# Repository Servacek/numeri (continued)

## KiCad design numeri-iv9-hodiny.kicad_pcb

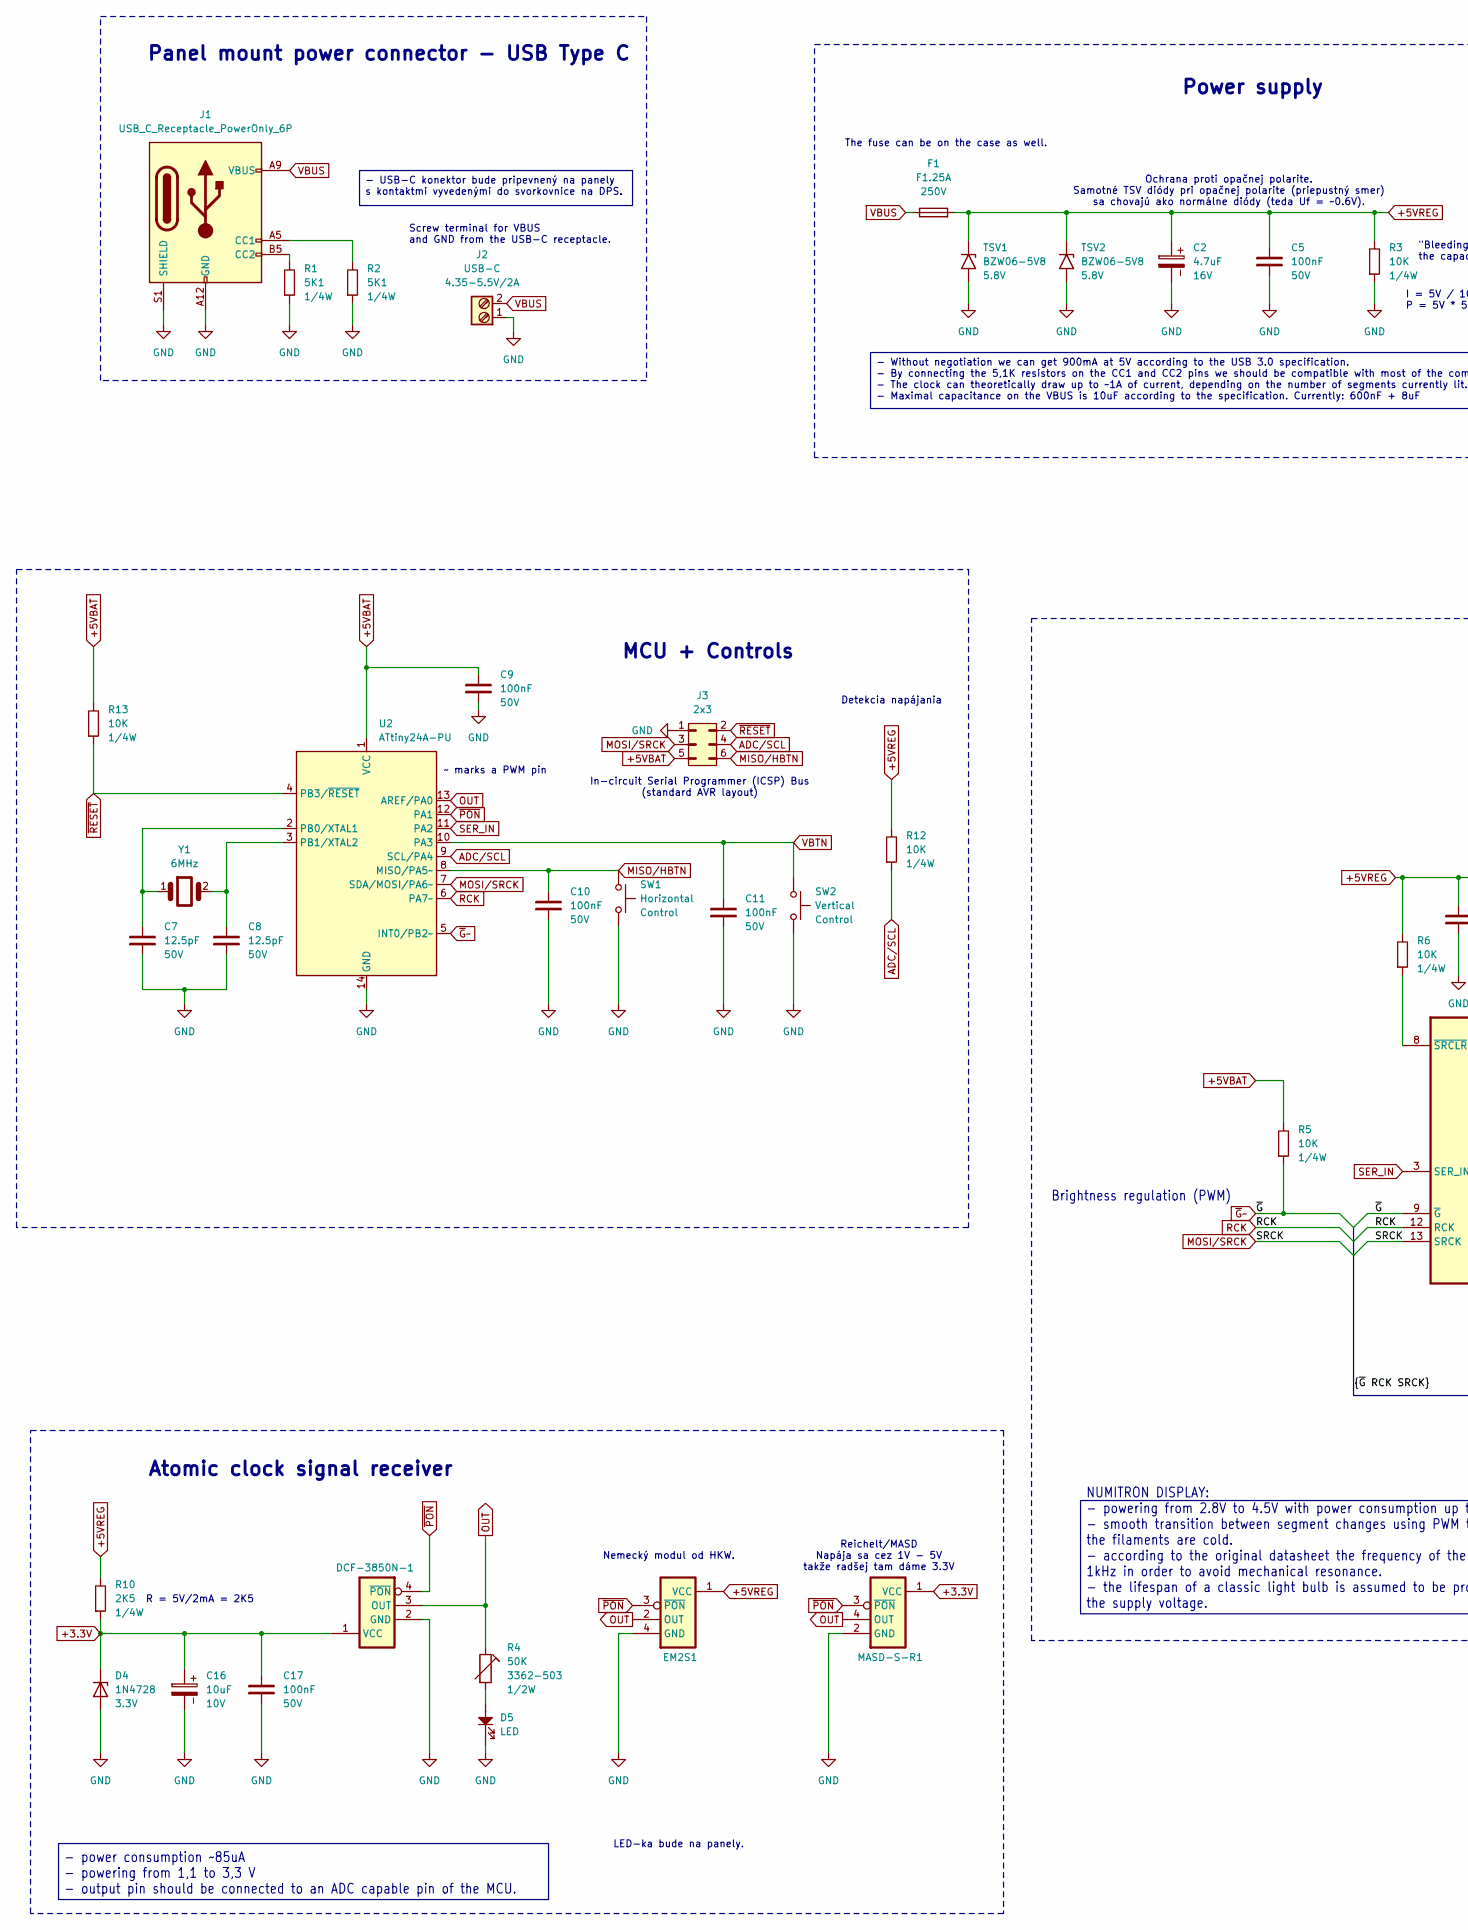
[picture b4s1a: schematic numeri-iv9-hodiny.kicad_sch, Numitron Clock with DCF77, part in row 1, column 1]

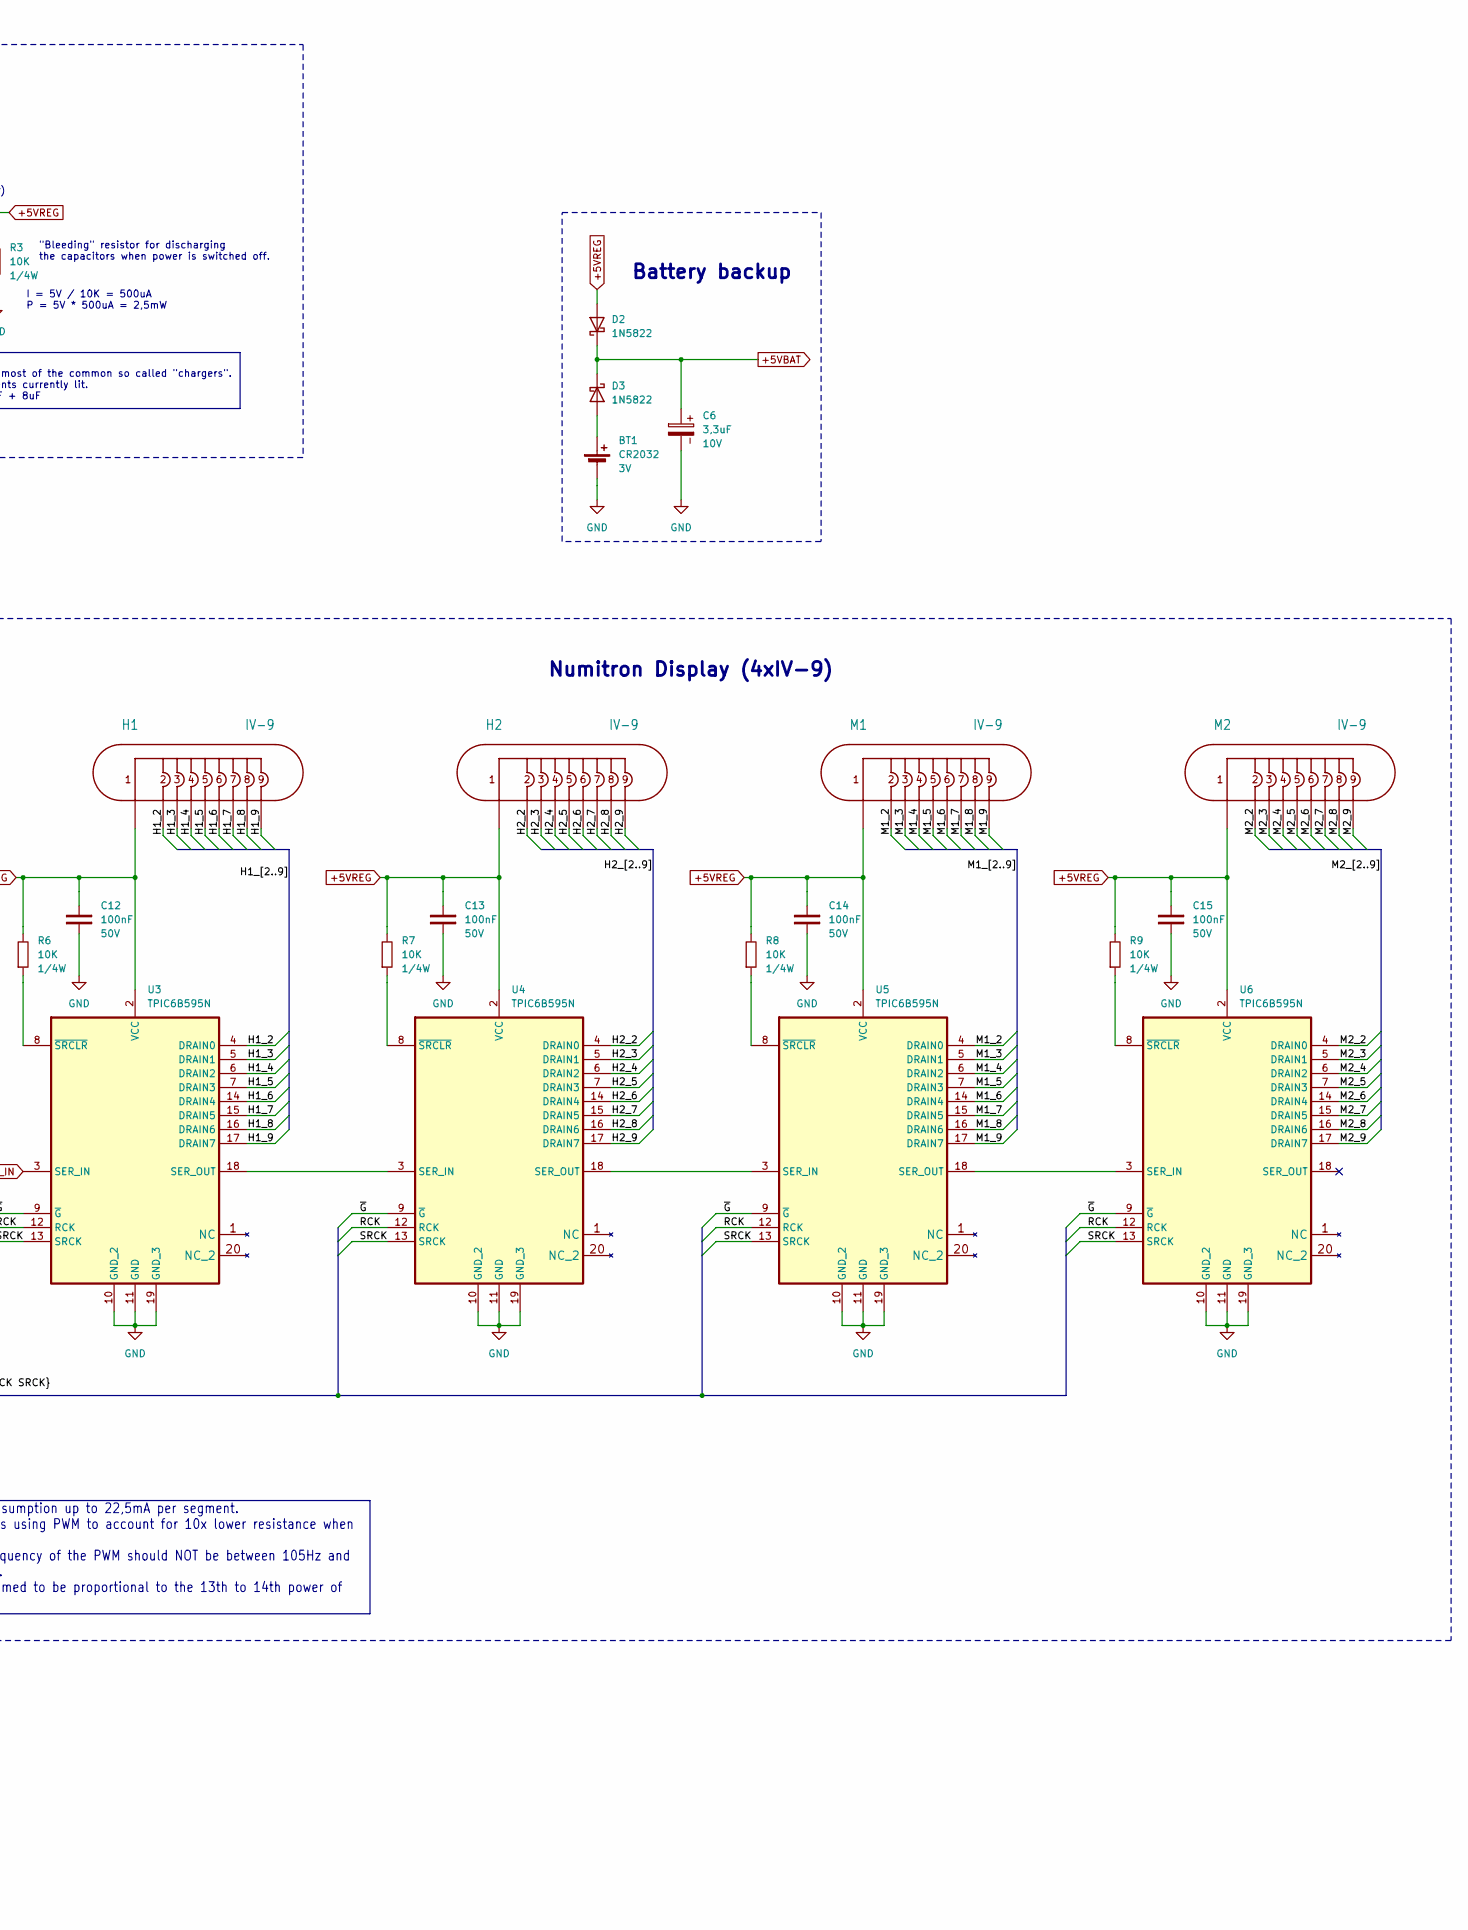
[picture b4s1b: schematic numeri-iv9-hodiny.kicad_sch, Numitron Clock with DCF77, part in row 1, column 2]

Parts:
BT1: CR2032; BatteryHolder_Keystone_CR2032_Vertical; Voltage 3V
C2: 4.7uF; CP_Radial_D5.0mm_P2.00mm; Voltage 16V
C5, C9, C10, C11, C12, C13, C14, C15, C17: 100nF; C_Disc_D3.0mm_W2.0mm_P2.50mm
C6: 3,3uF; CP_Radial_D5.0mm_P2.00mm; Voltage 10V
C7, C8: 12.5pF; C_Disc_D3.0mm_W2.0mm_P2.50mm
C16: 10uF; CP_Radial_D5.0mm_P2.00mm
D2, D3: 1N5822; D_DO-41_SOD81_P10.16mm_Horizontal
D4: 1N4728; D_DO-41_SOD81_P10.16mm_Horizontal
D5: LED; TerminalBlock_Phoenix_MPT-0,5-2-2.54_1x02_P2.54mm_Horizontal
DCF-3850N-1: DCF77; PinSocket_1x04_P2.54mm_Vertical
EM2S1: DCF77; PinSocket_1x04_P2.54mm_Vertical
F1: F1.25A; Fuseholder_Cylinder-5x20mm_Schurter_0031_8201_Horizontal_Op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; Voltage 250V
H1, H2: IV-9; IV-9_External_Socket_Asymetric
J1: USB_C_Receptacle_PowerOnly_6P
J2: USB-C; TerminalBlock_Phoenix_PT-1,5-2-5.0-H_1x02_P5.00mm_Horizontal
J3: 2x3; PinHeader_2x03_P2.54mm_Vertical
M1, M2: IV-9; IV-9_External_Socket_Asymetric
MASD-S-R1: DCF77; PinSocket_1x04_P2.54mm_Vertical
R1, R2: 5K1; R_Axial_DIN0207_L6.3mm_D2.5mm_P10.16mm_Horizontal
R3: 10K; R_Axial_DIN0207_L6.3mm_D2.5mm_P2.54mm_Vertical
R4: 50K; potentiometer_3362P
R5, R12, R13: 10K; R_Axial_DIN0207_L6.3mm_D2.5mm_P5.08mm_Vertical
R6, R7, R8, R9: 10K; R_Axial_DIN0207_L6.3mm_D2.5mm_P10.16mm_Horizontal
R10: 2K5; R_Axial_DIN0207_L6.3mm_D2.5mm_P10.16mm_Horizontal
SW1: Horizontal; TerminalBlock_Phoenix_MPT-0,5-2-2.54_1x02_P2.54mm_Horizontal
SW2: Vertical; TerminalBlock_Phoenix_MPT-0,5-2-2.54_1x02_P2.54mm_Horizontal
TSV1, TSV2: BZW06-5V8; D_DO-201AE_P15.24mm_Horizontal; Voltage 5.8V
U2: ATtiny24A-PU; DIP-14_W7.62mm_Socket
U3, U4, U5, U6: TPIC6B595N; DIP-20_W7.62mm_Socket
Y1: 6MHz; Crystal_HC49-4H_Vertical

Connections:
+3.3V: C16.1, C17.2, D4.1 (K), DCF-3850N-1.1 (VCC), MASD-S-R1.1 (VCC), R10.1
+5VBAT: C6.1, C9.2, D2.1 (K), D3.1 (K), J3.5, R5.2, R13.2, U2.1 (VCC)
+5VREG: C2.1, C5.2, C12.2, C13.2, C14.2, C15.2, D2.2 (A), EM2S1.1 (VCC), F1.2, H1.1, H2.1, M1.1, M2.1, R3.2, R6.2, R7.2, R8.2, R9.2, R10.2, R12.2, TSV1.1 (A1), TSV2.1 (A1), U3.2 (VCC), U4.2 (VCC), U5.2 (VCC), U6.2 (VCC)
/H1_2: H1.2, U3.4 (DRAIN0)
/H1_3: H1.3, U3.5 (DRAIN1)
/H1_4: H1.4, U3.6 (DRAIN2)
/H1_5: H1.5, U3.7 (DRAIN3)
/H1_6: H1.6, U3.14 (DRAIN4)
/H1_7: H1.7, U3.15 (DRAIN5)
/H1_8: H1.8, U3.16 (DRAIN6)
/H1_9: H1.9, U3.17 (DRAIN7)
/H2_2: H2.2, U4.4 (DRAIN0)
/H2_3: H2.3, U4.5 (DRAIN1)
/H2_4: H2.4, U4.6 (DRAIN2)
/H2_5: H2.5, U4.7 (DRAIN3)
/H2_6: H2.6, U4.14 (DRAIN4)
/H2_7: H2.7, U4.15 (DRAIN5)
/H2_8: H2.8, U4.16 (DRAIN6)
/H2_9: H2.9, U4.17 (DRAIN7)
/M1_2: M1.2, U5.4 (DRAIN0)
/M1_3: M1.3, U5.5 (DRAIN1)
/M1_4: M1.4, U5.6 (DRAIN2)
/M1_5: M1.5, U5.7 (DRAIN3)
/M1_6: M1.6, U5.14 (DRAIN4)
/M1_7: M1.7, U5.15 (DRAIN5)
/M1_8: M1.8, U5.16 (DRAIN6)
/M1_9: M1.9, U5.17 (DRAIN7)
/M2_2: M2.2, U6.4 (DRAIN0)
/M2_3: M2.3, U6.5 (DRAIN1)
/M2_4: M2.4, U6.6 (DRAIN2)
/M2_5: M2.5, U6.7 (DRAIN3)
/M2_6: M2.6, U6.14 (DRAIN4)
/M2_7: M2.7, U6.15 (DRAIN5)
/M2_8: M2.8, U6.16 (DRAIN6)
/M2_9: M2.9, U6.17 (DRAIN7)
ADC/SCL: J3.4, R12.1, U2.9 (SCL/PA4)
GND: BT1.2 (-), C2.2, C5.1, C6.2, C7.1, C8.1, C9.1, C10.1, C11.1, C12.1, C13.1, C14.1, C15.1, C16.2, C17.1, D4.2 (A), D5.1, DCF-3850N-1.2 (GND), EM2S1.4 (GND), J1.A12 (GND), J1.B12 (GND), J1.S1 (SHIELD), J2.1, J3.1, MASD-S-R1.2 (GND), R1.1, R2.1, R3.1, SW1.2, SW2.2, TSV1.2 (A2), TSV2.2 (A2), U2.14 (GND), U3.10 (GND_2), U3.11 (GND), U3.19 (GND_3), U4.10 (GND_2), U4.11 (GND), U4.19 (GND_3), U5.10 (GND_2), U5.11 (GND), U5.19 (GND_3), U6.10 (GND_2), U6.11 (GND), U6.19 (GND_3)
MISO/HBTN: C10.2, J3.6, SW1.1, U2.8 (MISO/PA5~)
MOSI/SRCK: J3.3, U2.7 (SDA/MOSI/PA6~), U3.13 (SRCK), U4.13 (SRCK), U5.13 (SRCK), U6.13 (SRCK)
unnamed: BT1.1 (+), D3.2 (A)
unnamed: D5.2, R4.2
unnamed: J1.A5 (CC1), R2.2
unnamed: J1.B5 (CC2), R1.2
unnamed: C7.2, U2.2 (PB0/XTAL1), Y1.1
unnamed: C8.2, U2.3 (PB1/XTAL2), Y1.2
unnamed: U3.18 (SER_OUT), U4.3 (SER_IN)
unnamed: R6.1, U3.8 (~SRCLR)
unnamed: U4.18 (SER_OUT), U5.3 (SER_IN)
unnamed: R7.1, U4.8 (~SRCLR)
unnamed: U5.18 (SER_OUT), U6.3 (SER_IN)
unnamed: R8.1, U5.8 (~SRCLR)
unnamed: R9.1, U6.8 (~SRCLR)
OUT: DCF-3850N-1.3 (OUT), EM2S1.2 (OUT), MASD-S-R1.4 (OUT), R4.1, U2.13 (AREF/PA0)
RCK: U2.6 (PA7~), U3.12 (RCK), U4.12 (RCK), U5.12 (RCK), U6.12 (RCK)
SER_IN: U2.11 (PA2), U3.3 (SER_IN)
VBTN: C11.2, SW2.1, U2.10 (PA3)
VBUS: F1.1, J1.A9 (VBUS), J1.B9 (VBUS), J2.2
~G~: R5.1, U2.5 (INT0/PB2~), U3.9 (~G), U4.9 (~G), U5.9 (~G), U6.9 (~G)
~PON: DCF-3850N-1.4 (~PON), EM2S1.3 (~PON), MASD-S-R1.3 (~PON), U2.12 (PA1)
~RESET: J3.2, R13.1, U2.4 (PB3/~RESET)

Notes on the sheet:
In-circuit Serial Programmer (ICSP) Bus (standard AVR layout)
The fuse can be on the case as well.
"Bleeding" resistor for discharging the capacitors when power is switched off.
Reichelt/MASD Napája sa cez 1V - 5V takže radšej tam dáme 3.3V
~ marks a PWM pin
Power supply
Battery backup
Screw terminal for VBUS and GND from the USB-C receptacle.
Detekcia napájania
I = 5V / 10K = 500uA P = 5V * 500uA = 2,5mW
MCU + Controls
Brightness regulation (PWM)
Ochrana proti opačnej polarite. Samotné TSV diódy pri opačnej polarite (priepustný smer) sa chovajú ako normálne diódy (teda Uf = ~0.6V).
Nemecký modul od HKW.
R = 5V/2mA = 2K5
LED-ka bude na panely.
Numitron Display (4xIV-9)
Atomic clock signal receiver
Panel mount power connector - USB Type C
NUMITRON DISPLAY: - powering from 2.8V to 4.5V with power consumption up to 22,5mA per segment. - smooth transition between segment changes using PWM to account for 10x lower resistance when the filaments are cold. - according to the original datasheet the frequency of the PWM should NOT be between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
- Without negotiation we can get 900mA at 5V according to the USB 3.0 specification. - By connecting the 5,1K resistors on the CC1 and CC2 pins we should be compatible with most of the common so called "chargers". - The clock can theoretically draw up to ~1A of current, depending on the number of s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
- power consumption ~85uA - powering from 1,1 to 3,3 V - output pin should be connected to an ADC capable pin of the MCU.
- USB-C konektor bude pripevnený na panely s kontaktmi vyvedenými do svorkovnice na DPS.

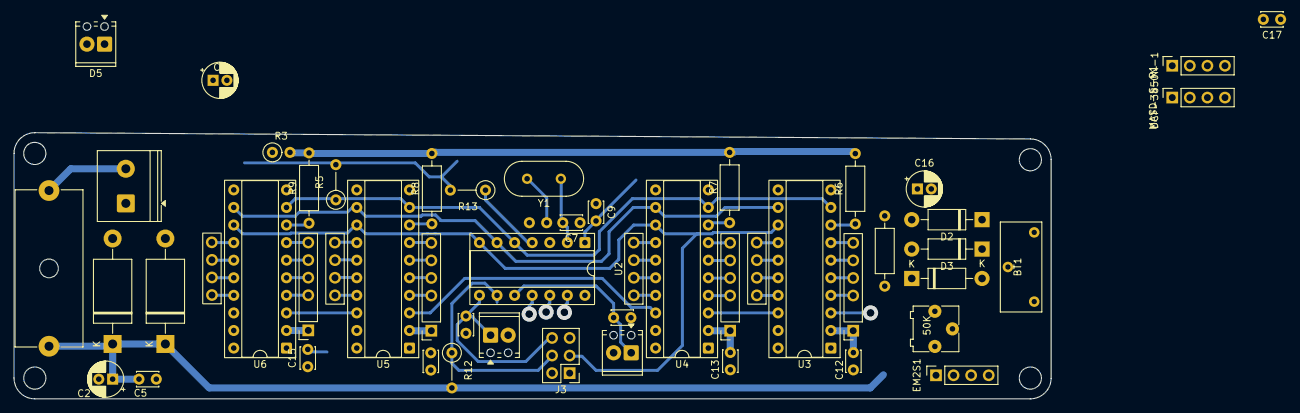
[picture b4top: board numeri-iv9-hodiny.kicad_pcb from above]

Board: 2 copper layers, 149.9 x 38.5 mm, 49 parts (1 on the bottom side), 58 nets.

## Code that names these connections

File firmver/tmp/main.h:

#ifndef NUMITRON_CLOCK_H
#define NUMITRON_CLOCK_H


#include <Arduino.h>
#include <EEPROM.h>


#define RESET_BUTTON        4
#define LEFT_BUTTON         3
#define RIGHT_BUTTON        2

#define LED_R               1 // PB1 (9 - 8)
#define LED_G               2 // PB2 (10 - 8)
#define LED_B               3 // PB3 (11 - 8)

#define DCF_OUT             A3 // PC3
#define DCF_PON             5  // PB5 (13 - 8)

#define LDR_PIN_PORTC       1 // A1

#define INA219_ADDR         0x40

// Tieto piny su uz pevne dane hardverom.
#define SERIN_PORTB         4 // PB4 (12 - 8)
#define SRCK_PORTB          0 // PB0 (8 - 8)
#define _G_PORTD            6 // PD6
#define RCK_PORTD           7 // PD7

#define SEGMENT_DP          7

#define DIGIT_COUNT         4

#define NUMBER_TRANS_DUR    3200 // ms
// Cim mensia hodnota, tym rychlejsie preklapanie.
#define CROSSFADING_WRAP    1
#define NUMBER_TRANS_PER    (NUMBER_TRANS_DUR / CROSSFADING_WRAP)

// Realne maximum je samozrejme 255 ale to by znamelo celych 5V pre numitrony
// co je nad maximalnu hodnotu stanovenu v dokumentacii.
// Takze mame hardverove maximum a softverove maximum.
#define MAX_BRIGHTNESS      127 //160
#define DEFAULT_BRIGHTNESS  MAX_BRIGHTNESS / 2
#define MINIMUM_BRIGHTNESS  10

#define DIGIT_MIN_UNITS     3
#define DIGIT_MIN_TENS      2
#define DIGIT_HOR_UNITS     1
#define DIGIT_HOR_TENS      0

#define DIGIT_MASK          0b01111111 // mask non-digit segments

#define EDIT_MODE_BLINK_F   200 // ms

#define LONG_PRESS_DELAY    2000 // ms

#define ON                  1
#define OFF                 0

#define PRESSED             0
#define RELEASED            1

#define NUM_SYMBOL_COUNT    10

#define MAX_MINUTES_COUNT   (24 * 60)

// Bit helpers
#define BIS(reg, bit)       (reg & (1 << bit))
#define SBI(reg, bit)       (reg |= (1 << bit))
#define CBI(reg, bit)       (reg &= ~(1 << bit))

#define PWM_REGISTER        OCR0A

// trvanie = 1 / 16 000 000 = 6,25 * 10^-8 s = 62,5 ns
#define NOP __asm__ __volatile__ ("nop\n\t")

// const byte CROSSFADING_FLIP_VALUES[] PROGMEM = {
//   20, 18, 16, 14, 13, 11, 10, 9, 8, 7, 6, 5, 4, 3, 2, 1
// };

// ---- EEPROM configuration addresses & enums ----
enum CONFIG {
  HOURS,
  MINUTES,
  BRIGHTNESS,
  GENERAL, // bit positions according to CONFIG_GENERAL
};

enum CONFIG_GENERAL {
  M12_24,        // 12/24h mode
  TRAILLING_ZERO, // show leading tens-hour zero
  NIGHT_MODE_ENABLED,
  NIGHT_MODE_TYPE,
};

// inline void SET(uint8_t pin, bool state) {
//     if (pin < 0) {
//         return;
//     }

//     if (pin <= 7) {
//         if (state) {
//             SBI(PORTD, pin);
//         } else {
//             CBI(PORTD, pin);
//         }
//     } else if (pin <= 13) {
//         if (state) {
//             SBI(PORTB, pin - 8);
//         } else {
//             CBI(PORTB, pin - 8);
//         }
//     } else if (pin <= A6) {
//         if (state) {
//             SBI(PORTC, pin - A0);
//         } else {
//             CBI(PORTC, pin - A0);
//         }
//     }
// }

// ---- Externs for globals defined in the sketch (.ino/.cpp) ----
extern byte LAZY_EE[];                    // lazy EEPROM cache
extern const byte NUM_SYMBOL_BYTES[];     // 7-seg bitmap -> symbol mapping

extern volatile bool edit_mode;
extern volatile bool diagnostics_mode;
extern volatile uint8_t selected_digit;

extern uint8_t segments_lit;

extern volatile uint8_t configured_brightness;
extern volatile bool number_transition;

extern volatile uint8_t blink_timer_counter;
extern volatile uint16_t brightness_counter;

extern volatile uint16_t minutes_count;

// ---- Function prototypes (public API used across translation units) ----

// EEPROM helpers
byte getEEConfig(uint8_t address);
void setEEConfig(uint8_t address, byte value);
void saveEEConfig();

// Editing / display helpers
void enterEditMode();
void exitEditMode();
uint8_t getSelectedNumSymbolIndex(uint8_t digit);

// Brightness / transition
void startNumberTransition();
void stopNumberTransition();
void configBrightness(uint8_t value);
void setBrightness(uint8_t value);

// Low-level segment/register control
void setNumitronSegment(uint8_t digit, uint8_t index, bool state);
void toggleNumitronSegment(uint8_t digit, uint8_t index);
void setSelectedDigit(uint8_t digit);
void putDigitsToInputRegs(byte* digits, uint8_t n);
void pushToOutputRegs();
void showDigits();

// Time / display logic
void displayTime(uint16_t time_in_minutes);
void onNewMinute();

// Diagnostics
void startDiagnostics();
void stopDiagnostics();

// Button handlers / input
void onLeftButtonPressed();
void onLeftButtonReleased();
void onLeftButtonLongPressed();

void onRightButtonPressed();
void onRightButtonReleased();
void onRightButtonLongPressed();

void onBothButtonsPressed();
void onBothButtonsReleased();
void onBothButtonsLongPressed();

void handleInput();

// Standard Arduino entry points (implemented in sketch)
void setup();
void loop();

#endif // NUMITRON_CLOCK_H

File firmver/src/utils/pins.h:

/*
 * pins.h
 *
 *  Piny pre konfiguraciu vstupov a vystupov.
 */

#ifndef PINS_H
#define PINS_H

#include <avr/io.h>
#include <stdint.h>

// IO - Piny

#define L_BTN           PD3
#define R_BTN           PD2

#define RESET_BUTTON    PD4

#define DCF_OUT         PC3 // A3
#define DCF_PON         PB5 // (13 - 8)

#define LDR_PIN_PORTC   PC1 // A1

#define SERIN_PORTB     PB4 // (12 - 8)
#define SRCK_PORTB      PB0 // (8 - 8)
// !! Tento pin nikdy nemoze byt nastaveny na LOW.
#define _G_PORTD        PD5
#define RCK_PORTD       PD7

////////////////////////////////////

// Nastavy zadany pin na definovanu logicku hodnotu.
// Nastavujeme mod INPUT s pull-up rezistorom (~50K) takze logicka hodnota je "slaba",
// ale toto je asi ten najlepsi kompromis medzi bezpecnostou a odolnostou proti ruseniu.
#define UNUSED_PIN(port, pin)                                                  \
    do {                                                                       \
        DDR##port &= ~(1 << pin);                                              \
        PORT##port |= (1 << pin);                                              \
    } while (0)

#define SAVE_ADC_MODE()                                                        \
    const uint8_t _saved_admux  = ADMUX;                                       \
    const uint8_t _saved_adcsra = ADCSRA;                                      \
    const uint8_t _saved_adcsrb = ADCSRB;

// ! KRITICKE PORADIE: ADCSRB musi byt obnovene PRED ADCSRA.
// Dovod: ak bol aktivny komparatorovy rezim (_saved_adcsrb ma ACME=1)
// a my najprv zapiseme ADCSRA s ADEN=1, nastane okno kde ACME=1 a ADEN=1
// existuju sucasne. Podla datasheetu ATmega328P §23.3: ked ACME=1 a ADEN=1,
// komparator pouziva AIN1 namiesto ADC multiplexora — vznika spurious ACO
// glitch ktory DCF77 ISR moze zachytit ako platny signal.
#define RESTORE_ADC_MODE()                                                     \
    ADCSRB = _saved_adcsrb;                                                    \
    ADCSRA = _saved_adcsra;                                                    \
    ADMUX  = _saved_admux;

////////////////////////////////////

static inline void COMPARATOR_ADC_MODE(uint8_t channel) {
    ADCSRA &= ~(1 << ADEN);                    // Vypneme ADC
    ADCSRB |= (1 << ACME);                     // Zapneme multiplexor
    ADMUX = (ADMUX & 0xF0) | (channel & 0x07); // Vyberieme kanal.
}

static inline void NORMAL_ADC_MODE() {
    ADCSRB &= ~(1 << ACME); // Vypneme multiplexor
    ADCSRA |= (1 << ADEN);  // Zapneme ADC
}

// Priame citanie ADC na ATmega328P.
// channel: cislo ADC kanalu (0-7), zodpoveda Arduino A0-A7.
// Predpoklada, ze ADC je uz v normalnom rezime (ADEN=1).
static inline uint16_t _ADC_READ(uint8_t channel) {
    // REFS0=1, REFS1=0 -> AVCC ako referencie (~5V).
    // Pouzivame vzdy AVCC pretoze AREF pin nie je na nasej DPS pouzity.
    ADMUX = (1 << REFS0) | (channel & 0x0F);

    // Zahodime prvu konverziu po prepnuti kanalu — S/H kondenzator potrebuje
    // cas na nabiti na novy vstup (podla datasheetu).
    ADCSRA |= (1 << ADSC);
    while (ADCSRA & (1 << ADSC));

    // Druha konverzia je presna.
    ADCSRA |= (1 << ADSC);
    while (ADCSRA & (1 << ADSC));

    return ADC; // 10-bitovy vysledok, 0-1023
}

static inline uint16_t ADC_READ_AND_RESTORE_MODE(const uint8_t channel)  {
    SAVE_ADC_MODE();
    NORMAL_ADC_MODE();
    const uint16_t value = _ADC_READ(channel);
    RESTORE_ADC_MODE();
    return value;
}

#endif // PINS_H

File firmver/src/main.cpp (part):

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    // Je lepsie ak nejaky pin ostane vo vzduchu ako by sme mali nieco poskodit.
    // !! Treba sa uistit, ze na tychto pinoch naozaj nie je nic pripojene.
    UNUSED_PIN(C, PC2);
    UNUSED_PIN(D, PD6);

    // PC6 - Pouzivame ako RESET

    #if !SERIAL_ENABLED
        // tieto piny sa pouzivaju len ak je serial zapnuty.
        UNUSED_PIN(D, PD0); // Serial RX
        UNUSED_PIN(D, PD1); // Serial TX

        UCSR0B &= ~((1<<TXEN0) | (1<<RXEN0));  // Vypneme tx/rx
        PRR |= (1 << PRUSART0); // Vypneme USART zbernicu.
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
    // I2C pull-upy - Wire ich nastavi sam cez Wire.begin(),
    // ale explicitne ich nastavime tu pre istotu
    PORTC |= (1 << PC4) | (1 << PC5);
    DDRC &= ~((1 << PC4) | (1 << PC5)); // vstup

    setup();

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
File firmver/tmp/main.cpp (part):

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    // akurat sa musime uistit, ze je tam zapnuty
    // pull-up rezistor kvoli definovanemu stavu.

    // piny PB6 a PB7 vyuzivame pre krystal.
    // DDRB    &= 0b00000011;
    // PORTB   |= 0b11111100;

    // DDRC     = 0b00000000;
    // PORTC    = 0b11111111;

    // // piny PD0 a PD1 vyuzivame pre Serial.
    // DDRD    &= 0b11111100;
    // PORTD   |= 0b11111100;

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
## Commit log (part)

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2025-05-28 migrácia na github
2025-06-02 Pridaný kód firmwaru + úpravy schéma a DPS s anglickým prekladom.
2025-06-02 Vylepšený firmware + EEPROM
2025-06-06 Veľké pokroky pri navrhu DPS.
2025-06-18 Pomerne velke zmeny a prehodnotenia zakladnych veci.
2025-06-18 some cache updates
2025-06-27 Zase po dlhej dobe nejaký zálohovací commit.
2025-07-09 preventivne
2025-07-12 Pridaný 3D model ktorý údajne pôjde zobraziť v Githube.
2025-07-13 preventívne
2025-07-13 obrazky
2025-07-16 Pridaná bloková schéma.
2025-07-16 úpravy README
2025-07-25 Prvá iterácia.
2025-07-25 STEP model
2025-07-25 Príručka v PDF formáte.
2025-08-05 Zase po dlhšej dobe preventívny commit.
2025-08-07 Aktualizovaný manuál a nejaké menšie zmeny.
2025-08-10 Záloha pred druhým tlačením.
2025-08-12 Úpravy stránky a firmvéru.
2025-08-19 Pridaný firmware.
2025-08-19 Úpravy firmvéru.
2025-08-22 Preventívne nahratie.
2025-08-24 Nove fotky.
2025-08-24 Opravene pdfka, fonty a možno aj model?
2025-08-24 Uz konecne fixnuty aj font, fotky zvacsene a bez interakcie.
2025-08-24 Odstraneny padding pre 3D model.
2025-08-31 Nahratý nový firmvér.
2025-09-08 Nové fotky a úpravy stránky.
2025-09-09 Pridané popisky.
2025-10-10 Ďalšie zmeny firmvéru.
2025-10-15 Mierne úpravy schémy, dopísanie niektorých častí príručky a pomerne rozsiahle opravy a optimalizácie firmvéru.
2025-10-19 Optimalizácie firmvéru.
2025-10-20 Ďalšie pomerne rozsiahle optimalizácie o opravy firmvéru.
2025-11-09 Preventívne uloženie na github.
2025-12-12 Opravy v schéme. Úpravy a optimalizácie firmvéru.
2025-12-14 Pridané views + opravy chýb.
2025-12-25 preventive commit.
2026-01-02 Po úpravach struktúry súborov programu, je program opäť kompilovateľný.
2026-02-23 Masivne upravy a opravy kodu. Pridany monitor pre monitorovanie prudoveho odberu displeja hodin.
2026-02-25 Dalsie masivne zmeny. Pridané casovace, aj ked zatial este moc nefunguju.
2026-03-01 Menšie úpravy firmvéru.
2026-03-07 Opravene niektore varovanie a ine chyby.
2026-03-21 Upravy firmvéru hodín, hlavnou zmenou je nový systém crossfadingu.
2026-03-22 A lot of refactoring changes.
2026-03-23 Pridaný led driver pre RGB ledku.
2026-04-13 Dalsie upravy fimrveru - zaloha.
2026-04-13 Finalizujeme refaktorizaciu.
2026-04-14 Pokracovanie v refaktorizacii firmveru.
2026-04-22 Aktualizacia firmveru.
2026-05-05 Upravený návrh dosky.
2026-05-05 updated gitignore
2026-05-05 Aktualizácia stránky, vylepšená galéria.
2026-05-11 Pridaný popisok projektu, zatiaľ skôr len obrázky.
2026-05-11 Prvotná implementácia služby pre monitorovanie displeja a ďalšie menšie úpravy firmvéru.
2026-05-19 Pravdepodobne posledná verzia príručky + drobné úpravy firmvéru.
2026-05-21 Vytlacena verzia prirucky + novy model, zatial v stadiu testovania.
2026-05-21 Pridany model s antenou +- finalna verzia.
2026-05-21 Presunuty web z /web do /docs aby fungovali github web pages.
2026-05-21 Optimalizovane a aktualizovane modely.
2026-05-21 Dalsie optimalizacie, oprava prirucky a schemy, aktualizacia schemy a odstranenie zbytocnych suborov.
2026-05-27 Aktualizácia fotiek a stránky.
2026-05-29 Event system.
2026-06-05 Velmi masívne finalizačné úpravy,
2026-06-08 - Opravene ukladanie casu aj ked nebol meneny. - Opravena chyba pri ktorej sa nezosynchronizovali sekundy pri DCF77 synchronizácií. - Opraveny systém zámkou pre LED. - Signalizácia nespravne nastaven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
2026-06-10 Pridaná časť "Video" na stránku a do README.md.
2026-06-10 Vypnuty debug mode.
2026-06-11 Aktualizovane video.
2026-06-11 Opravený nesprávne sa zobrazujúci font na mobile.
